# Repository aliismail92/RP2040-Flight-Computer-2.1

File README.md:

# RP2040-Flight-Computer-2.1
This is a custom drone flight computer based on RP2040. The KiCad files are available in addition to the production files to be produced by JLC PCB.

The Flight computer has the following sensors:
  - MPU 6050 Inertia sensor
  - LSM303 digital compass and accelerometer sensor
  - BMP280 pressure sensor

Specific features:

  - Uses usb Type C.
  - SD-card connector at the bottom of the board
  - Two uart connectors for the Radio controller (tagged IBUS) and another for GPS (tagged GPS)
  - Broken GPIOs for NRF24L01 for telemetry with proper pin locations
  - Buzzer

The two I2C ports connected to the MPU6050, BMP280, and LSM303 sensors have the pins exposed for debugging purposes.

The board was produced and assembled by JLCPCB and is working.

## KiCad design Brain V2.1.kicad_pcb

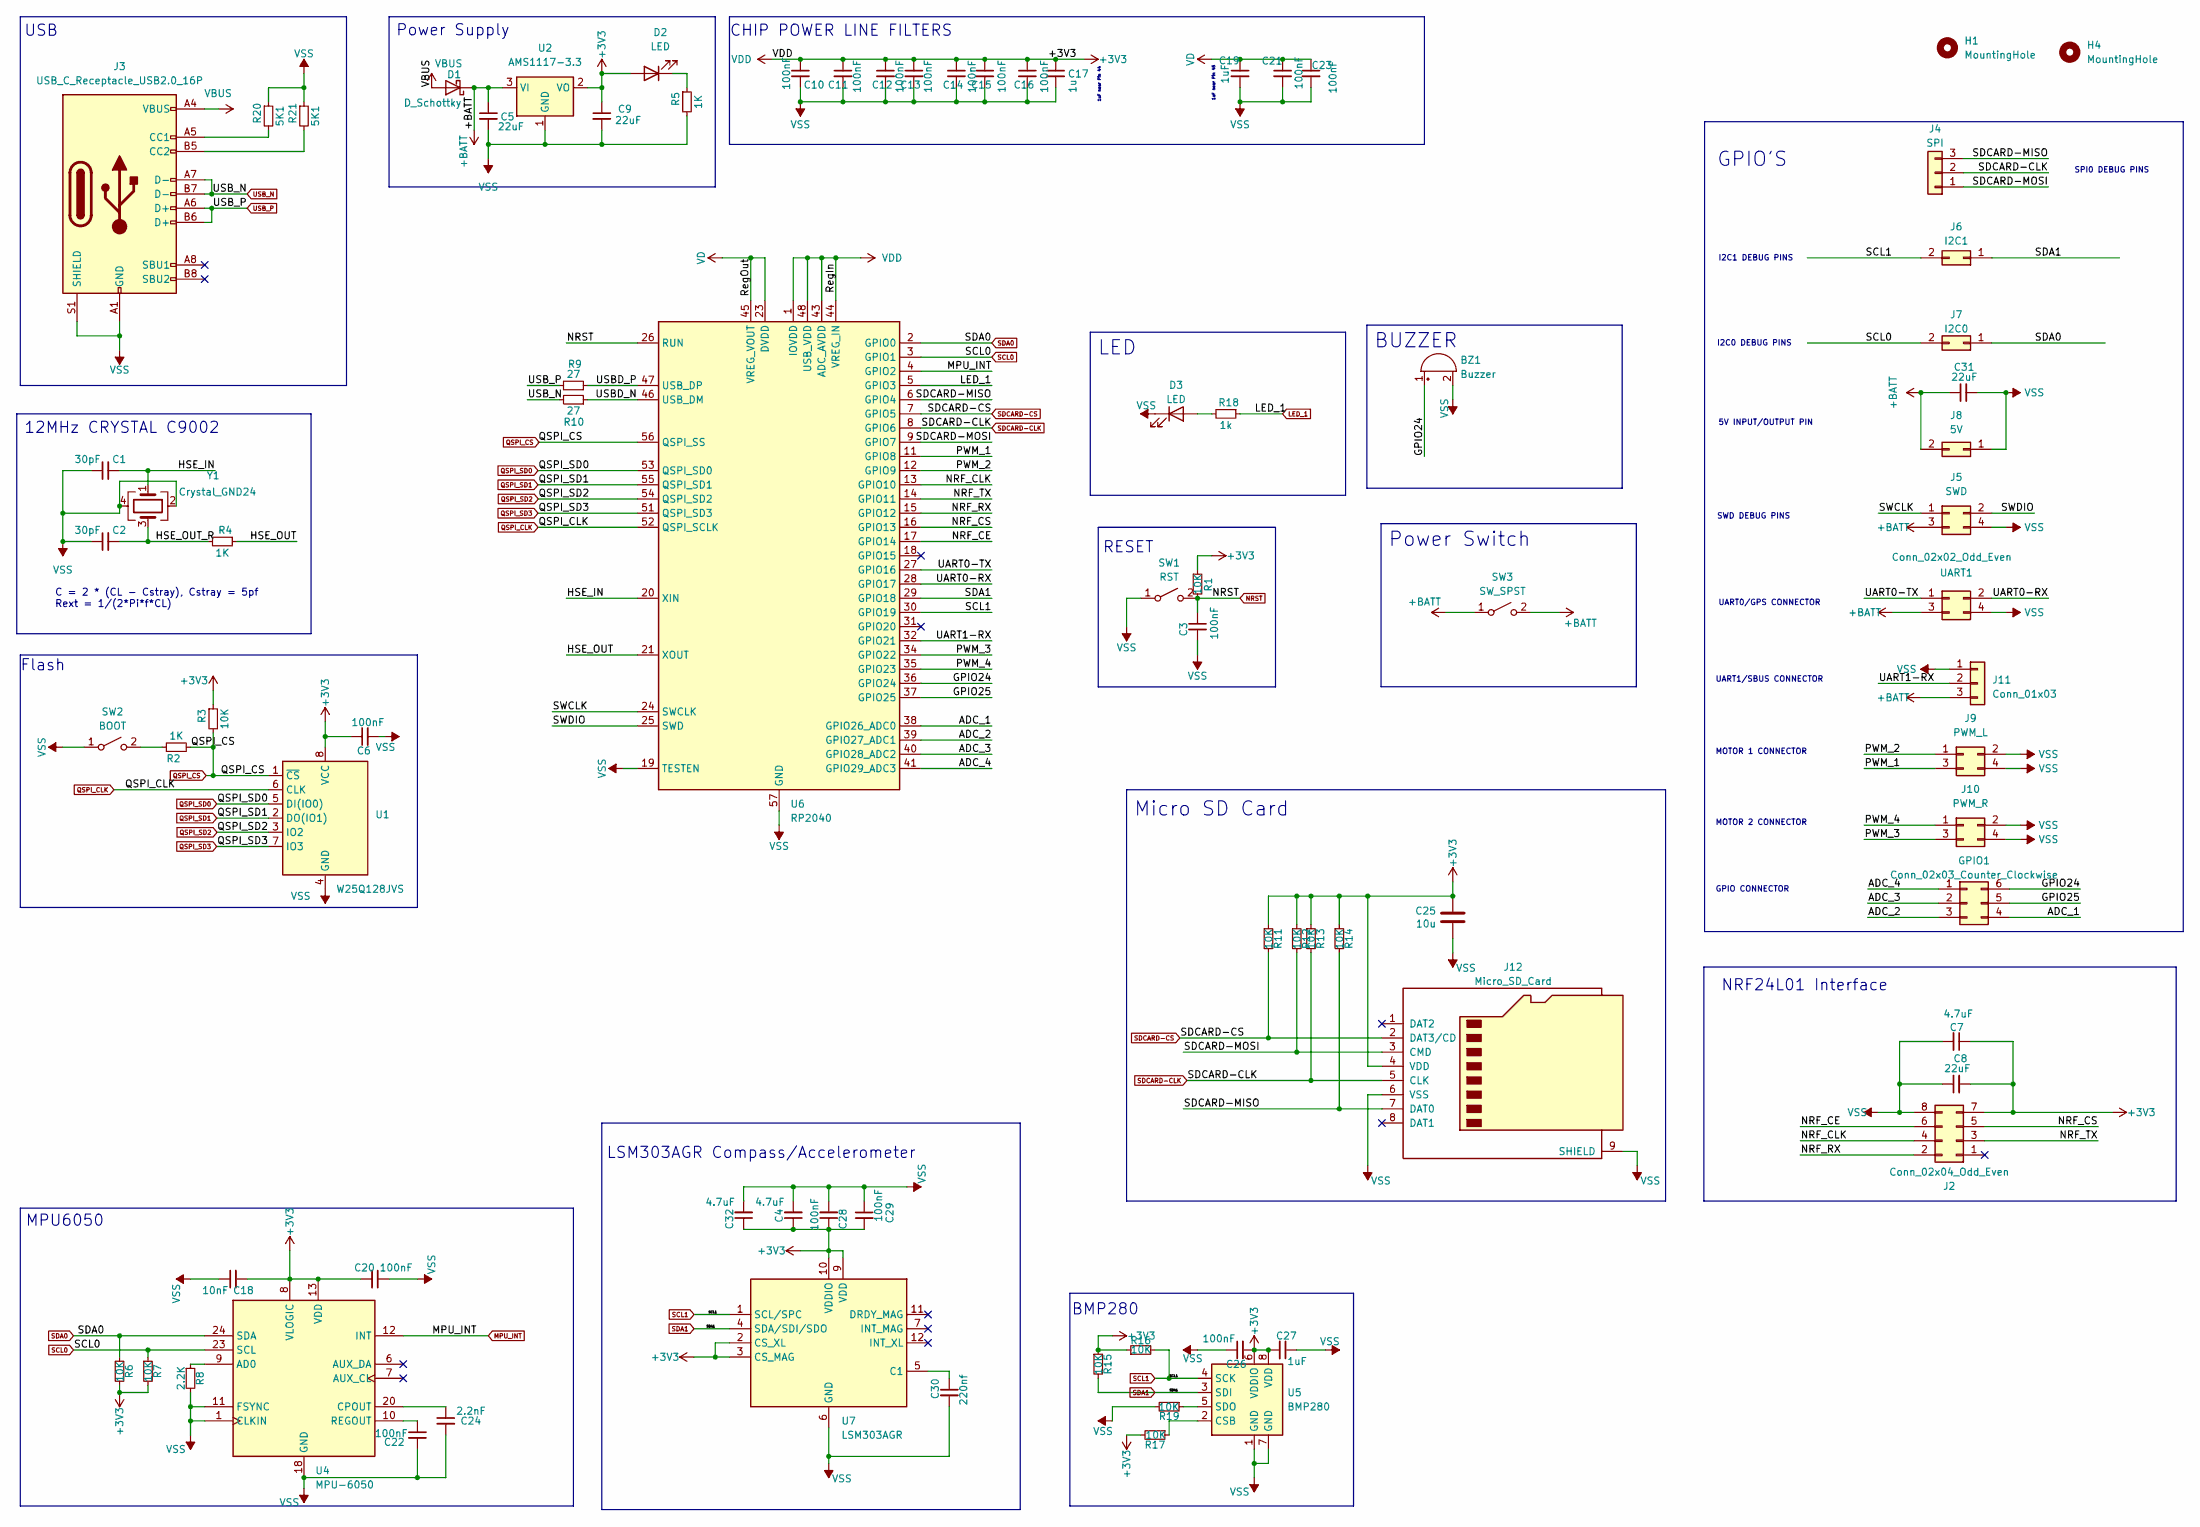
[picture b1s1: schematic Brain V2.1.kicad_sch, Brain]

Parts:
BZ1: Buzzer; Buzzer_12x9.5RM7.6
C1, C2: 30pF; C_0402_1005Metric
C3, C6, C10, C11, C12, C13, C14, C15, C16, C20, C21, C22, C23, C26, C28, C29: 100nF; C_0402_1005Metric
C4, C7, C32: 4.7uF; C_0603_1608Metric
C5, C8, C9, C31: 22uF; C_0603_1608Metric
C17: 1u; C_0402_1005Metric_Pad0.74x0.62mm_HandSolder
C18: 10nF; C_0402_1005Metric
C19: 1uF; C_0402_1005Metric_Pad0.74x0.62mm_HandSolder
C24: 2.2nF; C_0603_1608Metric
C25: 10u; C_0603_1608Metric
C27: 1uF; C_0402_1005Metric
C30: 220nf; C_0402_1005Metric
D1: D_Schottky; D_SMA
D2, D3: LED; LED_0603_1608Metric
GPIO1: Conn_02x03_Counter_Clockwise; PinHeader_2x03_P2.54mm_Vertical
H1, H4: MountingHole; MountingHole_4.3mm_M4
J2: Conn_02x04_Odd_Even; PinHeader_2x04_P2.54mm_Vertical
J3: USB_C_Receptacle_USB2.0_16P; USB_C_Receptacle_G-Switch_GT-USB-7010ASV
J4: SPI; PinHeader_1x03_P2.54mm_Vertical
J5: SWD; PinHeader_2x02_P2.54mm_Vertical
J6: I2C1; PinHeader_2x01_P2.54mm_Vertical
J7: I2C0; PinHeader_2x01_P2.54mm_Vertical
J8: 5V; PinHeader_2x01_P2.54mm_Vertical
J9: PWM_L; PinHeader_2x02_P2.54mm_Vertical
J10: PWM_R; PinHeader_2x02_P2.54mm_Vertical
J11: Conn_01x03; JST_XH_B3B-XH-AM_1x03_P2.50mm_Vertical
J12: Micro_SD_Card; microSD_HC_Molex_104031-0811
R1, R3, R6, R7, R11, R12, R13, R14, R15, R16, R17, R19: 10K; R_0402_1005Metric
R2, R4: 1K; R_0402_1005Metric
R5: 1K; R_0603_1608Metric
R8: 2.2K; R_0402_1005Metric
R9, R10: 27; R_0603_1608Metric
R18: 1k; R_0603_1608Metric
R20, R21: 5K1; R_0603_1608Metric
SW1: RST; SW_SPST_TL3342
SW2: BOOT; SW_SPST_TL3342
SW3: SW_SPST; SW_DIP_SPSTx01_Slide_9.78x4.72mm_W7.62mm_P2.54mm
U1: W25Q128JVS; SOIC-8_5.23x5.23mm_P1.27mm
U2: AMS1117-3.3; SOT-223-3_TabPin2
U4: MPU-6050; InvenSense_QFN-24_4x4mm_P0.5mm_NoMask
U5: BMP280; Bosch_LGA-8_2x2.5mm_P0.65mm_ClockwisePinNumbering
U6: RP2040; QFN-56-1EP_7x7mm_P0.4mm_EP4x4mm_ThermalVias
U7: LSM303AGR; LGA-12_2x2mm_P0.5mm
UART1: Conn_02x02_Odd_Even; JST_XH_B4B-XH-A_1x04_P2.50mm_Vertical
Y1: Crystal_GND24; Crystal_SMD_3225-4Pin_3.2x2.5mm

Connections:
+3V3: C4.1, C6.1, C7.1, C8.2, C9.1, C10.1, C11.1, C12.1, C13.1, C14.1, C15.1, C16.1, C17.1, C18.2, C20.2, C25.1, C26.2, C27.2, C28.1, C29.2, C32.1, D2.2 (A), J2.7, J12.4 (VDD), R1.1, R3.1, R6.2, R7.2, R11.1, R12.1, R13.1, R14.1, R15.1, R16.1, R17.2, U1.8 (VCC), U2.2 (VO), U4.8 (VLOGIC), U4.13 (VDD), U5.6 (VDDIO), U5.8 (VDD), U6.1 (IOVDD), U6.10 (IOVDD), U6.22 (IOVDD), U6.33 (IOVDD), U6.42 (IOVDD), U6.43 (ADC_AVDD), U6.44 (VREG_IN), U6.48 (USB_VDD), U6.49 (IOVDD), U7.2 (CS_XL), U7.3 (CS_MAG), U7.9 (VDD), U7.10 (VDDIO)
+BATT: C5.1, C31.1, D1.1 (K), J5.3, J8.2, J11.3, SW3.1 (A), SW3.2 (B), U2.3 (VI), UART1.3
/ADC_1: GPIO1.4, U6.38 (GPIO26_ADC0)
/ADC_2: GPIO1.3, U6.39 (GPIO27_ADC1)
/ADC_3: GPIO1.2, U6.40 (GPIO28_ADC2)
/ADC_4: GPIO1.1, U6.41 (GPIO29_ADC3)
/GPIO24: BZ1.1 (+), GPIO1.6, U6.36 (GPIO24)
/GPIO25: GPIO1.5, U6.37 (GPIO25)
/HSE_IN: C1.2, U6.20 (XIN), Y1.1
/HSE_OUT: R4.1, U6.21 (XOUT)
/HSE_OUT_R: C2.2, R4.2, Y1.3
/NRF_CE: J2.6, U6.17 (GPIO14)
/NRF_CLK: J2.4, U6.13 (GPIO10)
/NRF_CS: J2.5, U6.16 (GPIO13)
/NRF_RX: J2.2, U6.15 (GPIO12)
/NRF_TX: J2.3, U6.14 (GPIO11)
/PWM_1: J9.3, U6.11 (GPIO8)
/PWM_2: J9.1, U6.12 (GPIO9)
/PWM_3: J10.3, U6.34 (GPIO22)
/PWM_4: J10.1, U6.35 (GPIO23)
/SDCARD-MISO: J4.3, J12.7 (DAT0), R14.2, U6.6 (GPIO4)
/SDCARD-MOSI: J4.1, J12.3 (CMD), R12.2, U6.9 (GPIO7)
/SWCLK: J5.1, U6.24 (SWCLK)
/SWDIO: J5.2, U6.25 (SWD)
/UART0-RX: U6.28 (GPIO17), UART1.2
/UART0-TX: U6.27 (GPIO16), UART1.1
/UART1-RX: J11.2, U6.32 (GPIO21)
/USBD_N: R10.1, U6.46 (USB_DM)
/USBD_P: R9.1, U6.47 (USB_DP)
LED_1: R18.1, U6.5 (GPIO3)
MPU_INT: U4.12 (INT), U6.4 (GPIO2)
NRST: C3.1, R1.2, SW1.2 (B), U6.26 (RUN)
unnamed: D2.1 (K), R5.1
unnamed: D3.2 (A), R18.2
unnamed: J3.A5 (CC1), R20.2
unnamed: J3.B5 (CC2), R21.2
unnamed: R2.1, SW2.2 (B)
unnamed: R8.1, U4.9 (AD0)
unnamed: C24.1, U4.20 (CPOUT)
unnamed: C22.1, U4.10 (REGOUT)
unnamed: R17.1, U5.2 (CSB)
unnamed: R19.1, U5.5 (SDO)
unnamed: C30.1, U7.5 (C1)
QSPI_CLK: U1.6 (CLK), U6.52 (QSPI_SCLK)
QSPI_CS: R2.2, R3.2, U1.1 (~CS), U6.56 (QSPI_SS)
QSPI_SD0: U1.5 (DI(IO0)), U6.53 (QSPI_SD0)
QSPI_SD1: U1.2 (DO(IO1)), U6.55 (QSPI_SD1)
QSPI_SD2: U1.3 (IO2), U6.54 (QSPI_SD2)
QSPI_SD3: U1.7 (IO3), U6.51 (QSPI_SD3)
SCL0: J7.2, R7.1, U4.23 (SCL), U6.3 (GPIO1)
SCL1: J6.2, R16.2, U5.4 (SCK), U6.30 (GPIO19), U7.1 (SCL/SPC)
SDA0: J7.1, R6.1, U4.24 (SDA), U6.2 (GPIO0)
SDA1: J6.1, R15.2, U5.3 (SDI), U6.29 (GPIO18), U7.4 (SDA/SDI/SDO)
SDCARD-CLK: J4.2, J12.5 (CLK), R13.2, U6.8 (GPIO6)
SDCARD-CS: J12.2 (DAT3/CD), R11.2, U6.7 (GPIO5)
USB_N: J3.A7 (D-), J3.B7 (D-), R10.2
USB_P: J3.A6 (D+), J3.B6 (D+), R9.2
VBUS: D1.2 (A), J3.A4 (VBUS), J3.A9 (VBUS), J3.B4 (VBUS), J3.B9 (VBUS)
VD: C19.1, C21.1, C23.1, U6.23 (DVDD), U6.45 (VREG_VOUT), U6.50 (DVDD)
VSS: BZ1.2 (-), C1.1, C2.1, C3.2, C4.2, C5.2, C6.2, C7.2, C8.1, C9.2, C10.2, C11.2, C12.2, C13.2, C14.2, C15.2, C16.2, C17.2, C18.1, C19.2, C20.1, C21.2, C22.2, C23.2, C24.2, C25.2, C26.1, C27.1, C28.2, C29.1, C30.2, C31.2, C32.2, D3.1 (K), J2.8, J3.A1 (GND), J3.A12 (GND), J3.B1 (GND), J3.B12 (GND), J3.S1 (SHIELD), J5.4, J8.1, J9.2, J9.4, J10.2, J10.4, J11.1, J12.6 (VSS), J12.9 (SHIELD), R5.2, R8.2, R19.2, R20.1, R21.1, SW1.1 (A), SW2.1 (A), U1.4 (GND), U2.1 (GND), U4.1 (CLKIN), U4.11 (FSYNC), U4.18 (GND), U5.1 (GND), U5.7 (GND), U6.19 (TESTEN), U6.57 (GND), U7.6 (GND), U7.8 (GND), UART1.4, Y1.2, Y1.4

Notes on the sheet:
RESET
GPIO CONNECTOR
GPIO'S
UART1/SBUS CONNECTOR
SWD DEBUG PINS
5V INPUT/OUTPUT PIN
1uF near Pin 45
MPU6050
I2C0 DEBUG PINS
CHIP POWER LINE FILTERS
BMP280
12MHz CRYSTAL C9002
LED
Micro SD Card
SPI0 DEBUG PINS
LSM303AGR Compass/Accelerometer
NRF24L01 Interface
Flash
MOTOR 1 CONNECTOR
BUZZER
I2C1 DEBUG PINS
UART0/GPS CONNECTOR
C = 2 * (CL - Cstray), Cstray = 5pf Rext = 1/(2*Pi*f*CL)
MOTOR 2 CONNECTOR
Power Supply
USB
Power Switch
1uF near Pin 44

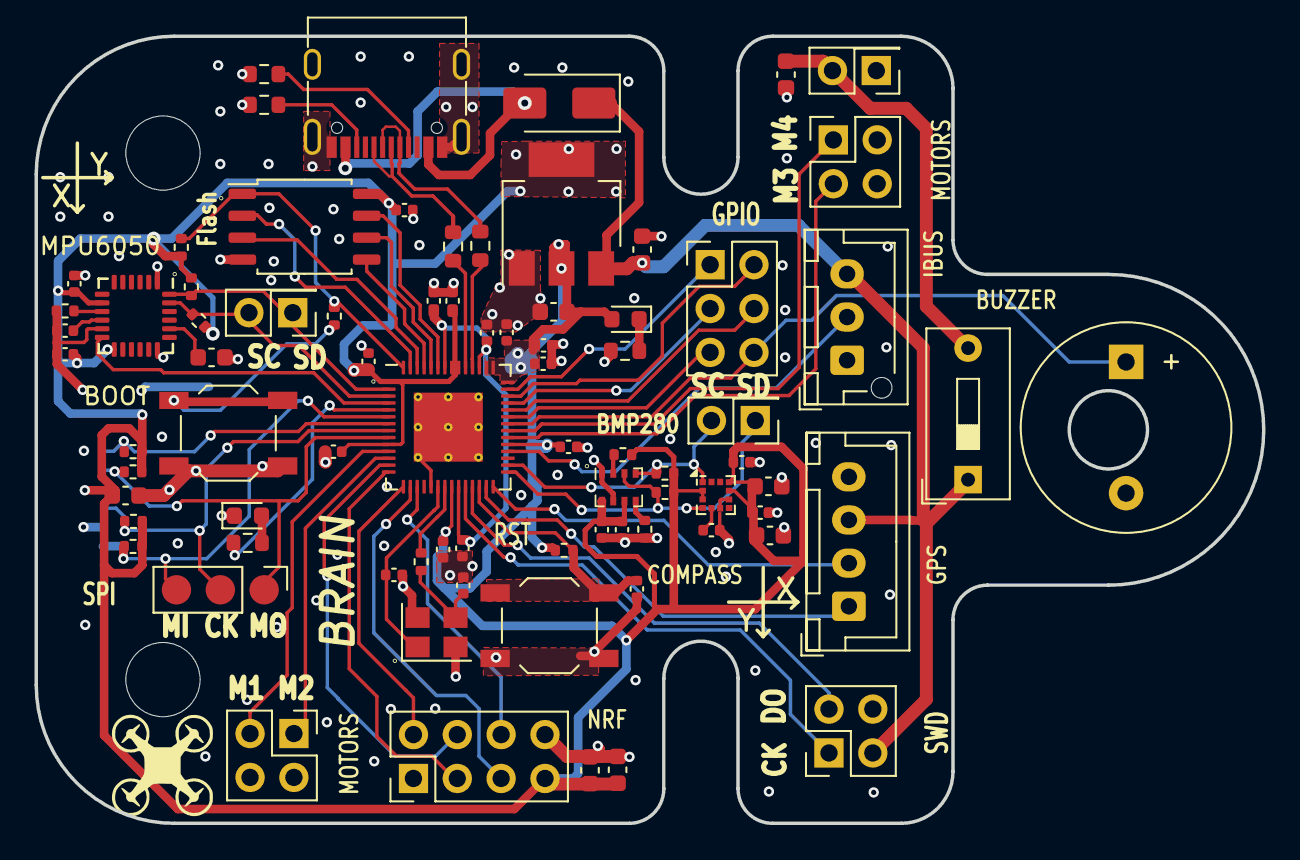
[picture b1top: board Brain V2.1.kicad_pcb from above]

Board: 4 copper layers, 71.1 x 45.6 mm, 82 parts (1 on the bottom side), 60 nets.
